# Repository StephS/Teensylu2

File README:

This board is a PROTOTYPE until the design is built and tested.

Version 0.9 is ready for production, earlier versions should not be used.

Please see Teensylu2_Pin_Map.htm for the correct pin mapping using the teensyduino library. Analog pins should use the analog pin reference.

The BOM is included. Please use parts of the same or higher ratings.

If you'd like to donate so I can buy the full version of Eagle, and make more cool stuff, please contact me through Google+

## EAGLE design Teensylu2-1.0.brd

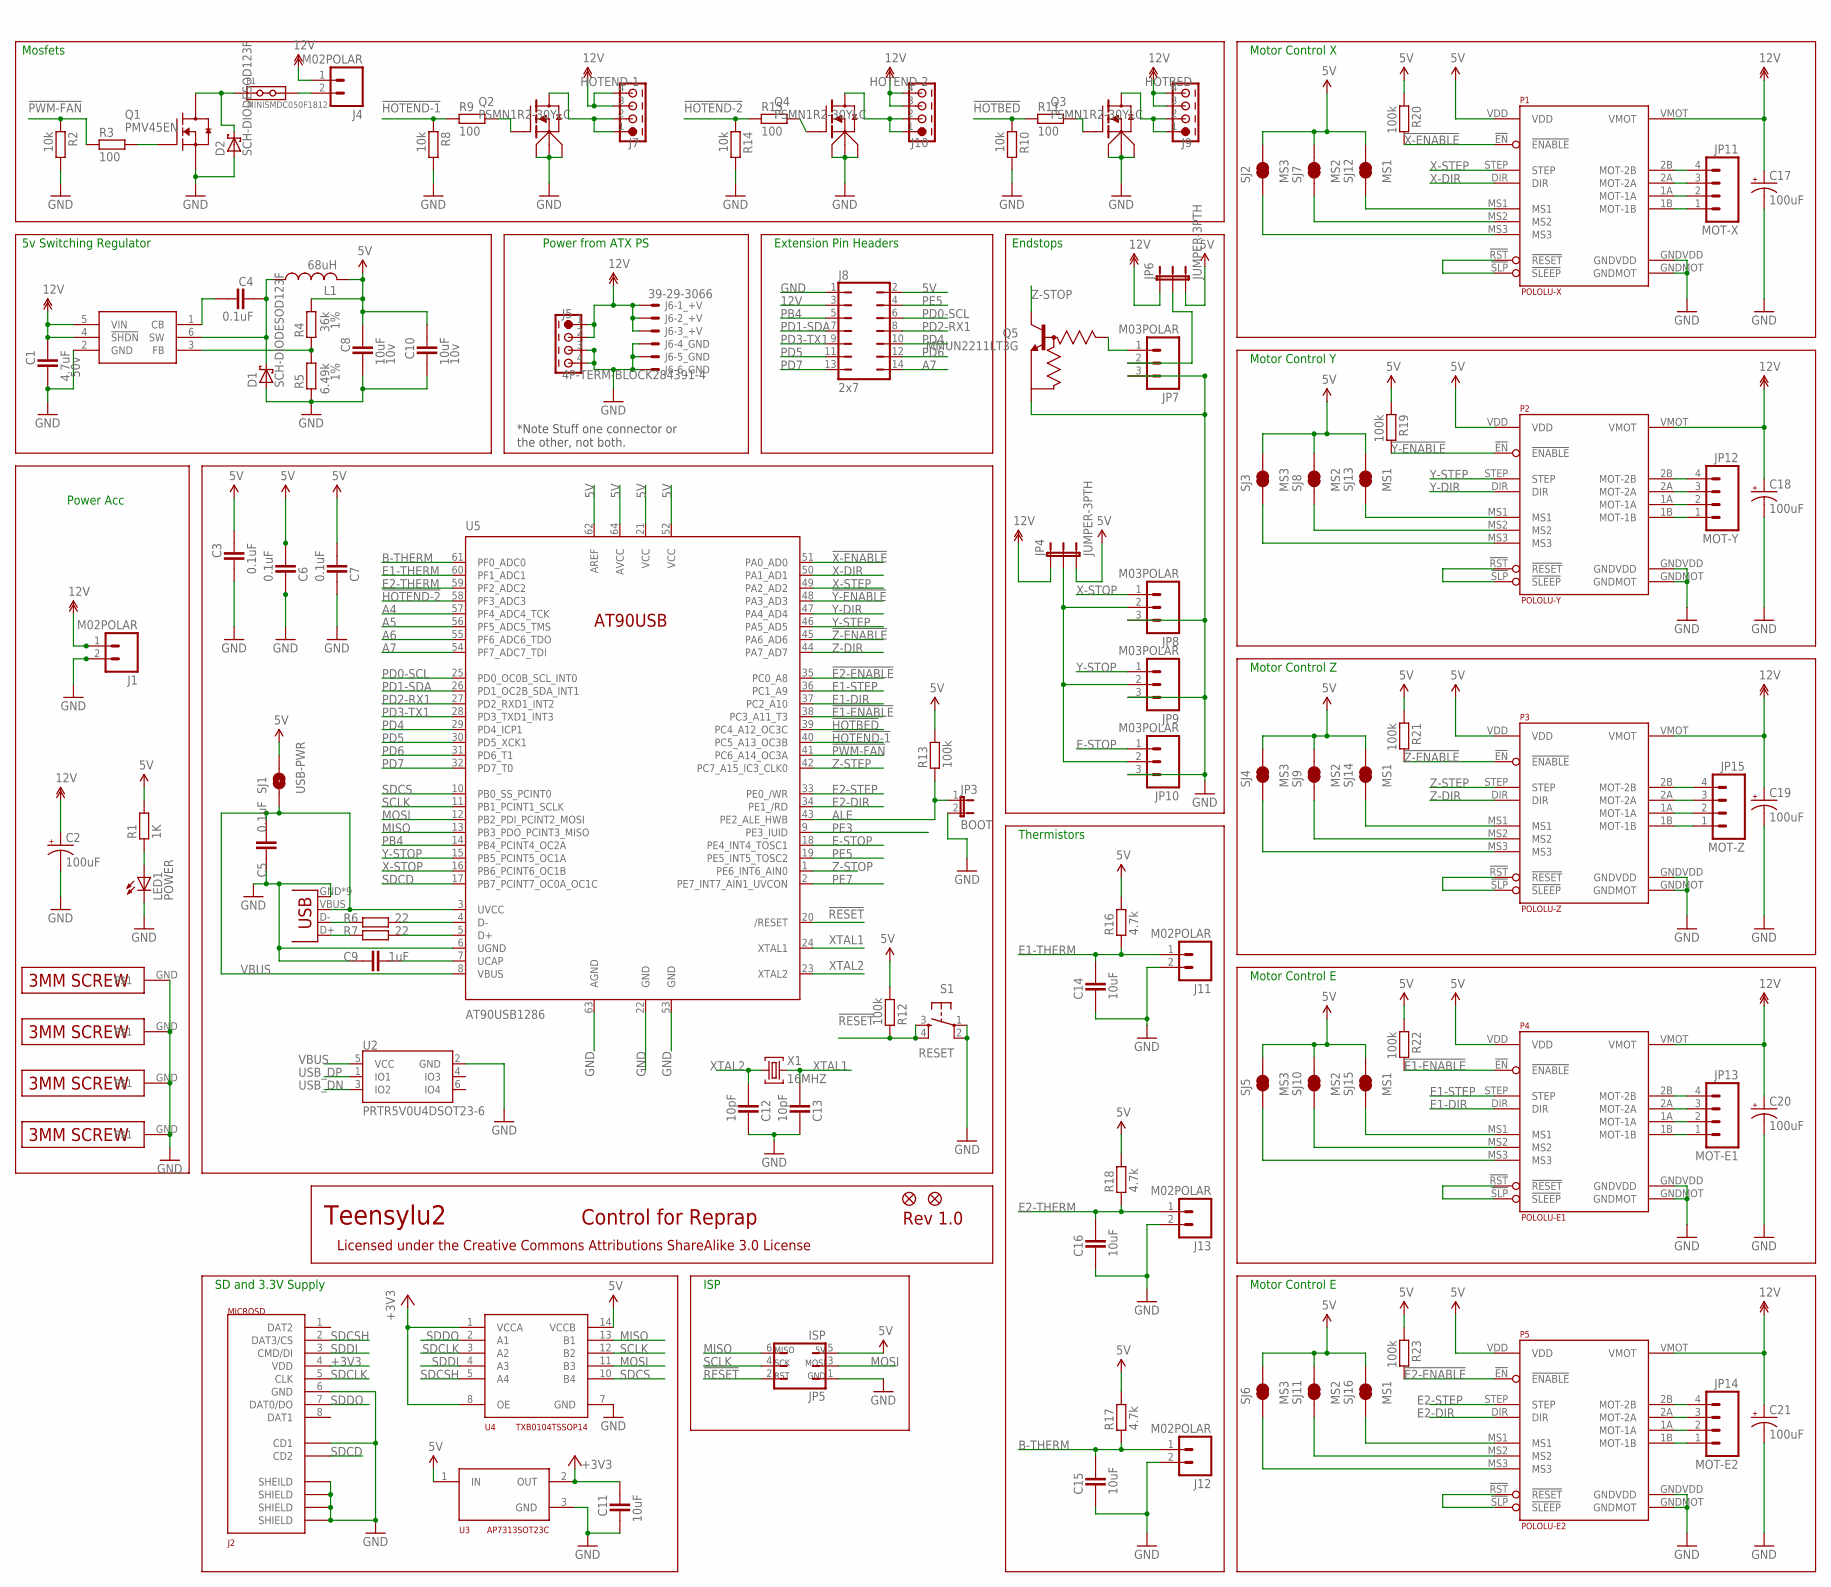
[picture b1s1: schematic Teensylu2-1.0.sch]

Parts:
C1: 4.7uF; CAPC3215X168N; TOLERANCE 10%; MANUFACTURER_PART_NUMBER UMK316AB7475KL-T
C2, C17, C18, C19, C20, C21: 100uF; PANASONIC_D; TOLERANCE 20%; MANUFACTURER_PART_NUMBER EEE-FTH101XAP
C3, C5, C6, C7: 0.1uF; CAPC1608X92N; TOLERANCE 10%; MANUFACTURER_PART_NUMBER GRM188R71C104KA01D
C4: 0.1uF; CAPC1608X92N; TOLERANCE 10%; MANUFACTURER_PART_NUMBER CL10B104KB8NNNC
C8, C10: 10uF; CAPC2012X145AN; TOLERANCE 10%; MANUFACTURER_PART_NUMBER GRM21BR71A106KE51L
C9: 1uF; CAPC1608X92N; TOLERANCE 20%; MANUFACTURER_PART_NUMBER CL10A105MO8NNNC
C11, C14, C15, C16: 10uF; CAPC1608X92N; TOLERANCE 20%; MANUFACTURER_PART_NUMBER GRM188R61C106MA73D
C12, C13: 10pF; CAPC1608X92N; TOLERANCE 5%; MANUFACTURER_PART_NUMBER CL10C100JB8NCNC
D1: SCH-DIODESOD123F; SOD123F; MANUFACTURER_PART_NUMBER PMEG4010CEH,115
D2: SCH-DIODESOD123F; SOD123F
F1: MINISMDC050F1812; MINISMDC
J1, J4, J11, J12, J13: M02POLAR; MOLEX-1X2; MANUFACTURER_PART_NUMBER 0022272021
J2: MICROSD; AMPHENOL-MICROSD
J3: USB-MICRO-PTH; USB-MICROB-PTH
J5: 4P-TERM-BLOCK284391-4; 284391-4
J6: 39-29-3066
J7: HOTEND-1; 282834-4
J8: 2x7; JP7Q; MANUFACTURER_PART_NUMBER M20-9980746
J9: HOTBED; 284391-4
J10: HOTEND-2; 282834-4
JP1, JP2: FIDUCIAL1X2.5; FIDUCIAL-1X2.5
JP3: BOOT; 1X02; MANUFACTURER_PART_NUMBER M20-9990246
JP4, JP6: JUMPER-3PTH; 1X03
JP5: ISP
JP7, JP8, JP9, JP10: M03POLAR; MOLEX-1X3; MANUFACTURER_PART_NUMBER 0022272031
JP11: MOT-X; MOLEX-1X4
JP12: MOT-Y; MOLEX-1X4
JP13: MOT-E1; MOLEX-1X4
JP14: MOT-E2; MOLEX-1X4
JP15: MOT-Z; MOLEX-1X4
L1: 68uH; SRN6045; MANUFACTURER_PART_NUMBER SRN6045-680M
LED1: POWER; CHIPLED_0805; MANUFACTURER_PART_NUMBER APT2012SGC
P1: POLOLU-X; POLOLU-STEPPER-PTH
P2: POLOLU-Y; POLOLU-STEPPER-PTH
P3: POLOLU-Z; POLOLU-STEPPER-PTH
P4: POLOLU-E1; POLOLU-STEPPER-PTH
P5: POLOLU-E2; POLOLU-STEPPER-PTH
Q1: PMV45EN; SOT23C; VOLTAGE 60V; MANUFACTURER_PART_NUMBER IRLML2060TRPBF
Q2, Q3, Q4: PSMN1R2-30YLC; LFPACK-POWERPAK-SO8
Q5: MMUN2211LT3G; SOT23C; MANUFACTURER_PART_NUMBER MMUN2211LT3G
R1: 1K; RESC1608X55N
R2, R8, R10, R14: 10k; RESC1608X55N
R3, R9, R11, R15: 100; RESC1608X55N
R4: 36k; RESC1608X55N; TOLERANCE 1%
R5: 6.49k; RESC1608X55N; TOLERANCE 1%
R6, R7: 22; RESC1608X55N
R12, R13, R19, R20, R21, R22, R23: 100k; RESC1608X55N
R16, R17, R18: 4.7k; RESC1608X55N
S1: RESET; TACTILE_SWITCH_SMD
SCREW1, SCREW2, SCREW3, SCREW4: 3MM-SCREW; PLATEDSCREW
SJ1: USB-PWR; SJ_2S-NO
SJ2, SJ3, SJ4, SJ5, SJ6: MS3; SJ_2S-TRACE
SJ7, SJ8, SJ9, SJ10, SJ11: MS2; SJ_2S-TRACE
SJ12, SJ13, SJ14, SJ15, SJ16: MS1; SJ_2S-TRACE
U1: LMR16006X; TSOT6
U2: PRTR5V0U4DSOT23-6; SOT23-6
U3: AP7313SOT23C; SOT23C
U4: TXB0104TSSOP14; TSSOP14
U5: AT90USB1286; TQFP64-2; MANUFACTURER_PART_NUMBER AT90USB1286
X1: 16MHZ; NDK-XTAL; MANUFACTURER_PART_NUMBER NX5032GA-16.000000MHZ-LN-CD-1

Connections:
5V: C3.1, C6.2, C7.2, C8.1, C10.1, J8.2, JP4.3, JP5.5, JP6.3, L1.2, P1.VDD, P2.VDD, P3.VDD, P4.VDD, P5.VDD, R1.2, R4.1, R12.2, R13.2, R16.2, R17.2, R18.2, R19.1, R20.1, R21.1, R22.1, R23.1, SJ1.2, SJ2.2, SJ3.2, SJ4.2, SJ5.2, SJ6.2, SJ7.2, SJ8.2, SJ9.2, SJ10.2, SJ11.2, SJ12.2, SJ13.2, SJ14.2, SJ15.2, SJ16.2, U3.1 (IN), U4.14 (VCCB), U5.21 (VCC), U5.52 (VCC), U5.62 (AREF), U5.64 (AVCC)
5VREG_CB: C4.2, U1.1 (CB)
5VREG_FB: R4.2, R5.1, U1.3 (FB)
5VREG_SW: C4.1, D1.C, L1.1, U1.6 (SW)
12V: C1.1, C2.+, C17.+, C18.+, C19.+, C20.+, C21.+, J1.1, J4.1, J5.1, J5.2, J6.1, J6.2, J6.3, J7.3, J7.4, J8.3, J9.3, J9.4, J10.3, J10.4, JP4.1, JP6.1, P1.VMOT, P2.VMOT, P3.VMOT, P4.VMOT, P5.VMOT, U1.4 (!SHDN), U1.5 (VIN)
!E1-ENABLE: P4.!EN (!ENABLE), R22.2, U5.38 (PC3_A11_T3)
!E2-ENABLE: P5.!EN (!ENABLE), R23.2, U5.35 (PC0_A8)
!HOTBED: R10.1, R11.1, U5.39 (PC4_A12_OC3C)
!HOTEND-1: R8.1, R9.1, U5.40 (PC5_A13_OC3B)
!HOTEND-2: R14.1, R15.1, U5.58 (PF3_ADC3)
!PWM-FAN: R2.1, R3.1, U5.41 (PC6_A14_OC3A)
!RESET: JP5.2, R12.1, S1.3, S1.4, U5.20 (/RESET)
!X-ENABLE: P1.!EN (!ENABLE), R20.2, U5.51 (PA0_AD0)
!Y-ENABLE: P2.!EN (!ENABLE), R19.2, U5.48 (PA3_AD3)
!Z-ENABLE: P3.!EN (!ENABLE), R21.2, U5.45 (PA6_AD6)
+3V3: C11.1, J2.4 (VDD), U3.2 (OUT), U4.1 (VCCA), U4.8 (OE)
A4: U5.57 (PF4_ADC4_TCK)
A5: U5.56 (PF5_ADC5_TMS)
A6: U5.55 (PF6_ADC6_TDO)
A7: J8.14, U5.54 (PF7_ADC7_TDI)
ALE: JP3.1, R13.1, U5.43 (PE2_ALE_HWB)
B-THERM: C15.2, J12.1, R17.1, U5.61 (PF0_ADC0)
E1-DIR: P4.DIR, U5.37 (PC2_A10)
E1-STEP: P4.STEP, U5.36 (PC1_A9)
E1-THERM: C14.2, J11.1, R16.1, U5.60 (PF1_ADC1)
E2-DIR: P5.DIR, U5.34 (PE1_/RD)
E2-MOT-1A: JP14.2, P5.1A (MOT-1A)
E2-MOT-1B: JP14.1, P5.1B (MOT-1B)
E2-MOT-2A: JP14.3, P5.2A (MOT-2A)
E2-MOT-2B: JP14.4, P5.2B (MOT-2B)
E2-STEP: P5.STEP, U5.33 (PE0_/WR)
E2-THERM: C16.2, J13.1, R18.1, U5.59 (PF2_ADC2)
E-MOT-1A: JP13.2, P4.1A (MOT-1A)
E-MOT-1B: JP13.1, P4.1B (MOT-1B)
E-MOT-2A: JP13.3, P4.2A (MOT-2A)
E-MOT-2B: JP13.4, P4.2B (MOT-2B)
E-MS1: P4.MS1, SJ15.1
E-MS2: P4.MS2, SJ10.1
E-MS3: P4.MS3, SJ5.1
E-MS4: P5.MS1, SJ16.1
E-MS5: P5.MS2, SJ11.1
E-MS6: P5.MS3, SJ6.1
E-RESETSLEEP: P4.!RST (!RESET), P4.!SLP (!SLEEP)
E-RESETSLEEP1: P5.!RST (!RESET), P5.!SLP (!SLEEP)
E-STOP: JP10.1, U5.18 (PE4_INT4_TOSC1)
ENDSTOP+V: JP4.2, JP8.2, JP9.2, JP10.2
GND: C1.2, C2.-, C3.2, C5.1, C6.1, C7.1, C8.2, C9.1, C10.2, C11.2, C12.1, C13.1, C14.1, C15.1, C16.1, C17.-, C18.-, C19.-, C20.-, C21.-, D1.A, D2.A, J1.2, J2.6 (GND), J2.C1 (SHEILD), J2.C2 (SHIELD), J2.C3 (SHIELD), J2.C4 (SHIELD), J2.CD1, J3.GND, J3.GND1 (GND), J3.GND2 (GND), J3.GND3 (GND), J3.GND4 (GND), J3.GND5 (GND), J3.GND6 (GND), J3.GND7 (GND), J3.GND8 (GND), J5.3, J5.4, J6.4, J6.5, J6.6, J8.1, J11.2, J12.2, J13.2, JP3.2, JP5.1, JP7.3, JP8.3, JP9.3, JP10.3, LED1.C, P1.GNDMOT, P1.GNDVDD, P2.GNDMOT, P2.GNDVDD, P3.GNDMOT, P3.GNDVDD, P4.GNDMOT, P4.GNDVDD, P5.GNDMOT, P5.GNDVDD, Q1.2 (S), Q2.1 (S1), Q2.2 (S2), Q2.3 (S3), Q3.1 (S1), Q3.2 (S2), Q3.3 (S3), Q4.1 (S1), Q4.2 (S2), Q4.3 (S3), Q5.2 (E), R2.2, R5.2, R8.2, R10.2, R14.2, S1.1, S1.2, SCREW1.GND, SCREW2.GND, SCREW3.GND, SCREW4.GND, U1.2 (GND), U2.2 (GND), U3.3 (GND), U4.7 (GND), U5.6 (UGND), U5.22 (GND), U5.53 (GND), U5.63 (AGND)
HOTBED-GND: J9.1, J9.2, Q3.5-8 (D)
HOTEND-GND: J7.1, J7.2, Q2.5-8 (D)
HOTEND-GND1: J10.1, J10.2, Q4.5-8 (D)
MISO: JP5.6, U4.13 (B1), U5.13 (PB3_PDO_PCINT3_MISO)
MOSI: JP5.3, U4.11 (B3), U5.12 (PB2_PDI_PCINT2_MOSI)
unnamed: LED1.A, R1.1
unnamed: Q3.4 (G), R11.2
unnamed: R6.2, U5.4 (D-)
unnamed: R7.2, U5.5 (D+)
unnamed: F1.P$2, J4.2
unnamed: D2.C, F1.P$1, Q1.3 (D)
unnamed: Q1.1 (G), R3.2
unnamed: Q2.4 (G), R9.2
unnamed: Q4.4 (G), R15.2
PB4: J8.5, U5.14 (PB4_PCINT4_OC2A)
PD0-SCL: J8.6, U5.25 (PD0_OC0B_SCL_INT0)
PD1-SDA: J8.7, U5.26 (PD1_OC2B_SDA_INT1)
PD2-RX1: J8.8, U5.27 (PD2_RXD1_INT2)
PD3-TX1: J8.9, U5.28 (PD3_TXD1_INT3)
PD4: J8.10, U5.29 (PD4_ICP1)
PD5: J8.11, U5.30 (PD5_XCK1)
PD6: J8.12, U5.31 (PD6_T1)
PD7: J8.13, U5.32 (PD7_T0)
PE3: U5.9 (PE3_IUID)
PE5: J8.4, U5.19 (PE5_INT5_TOSC2)
PE7: U5.2 (PE7_INT7_AIN1_UVCON)
SCLK: JP5.4, U4.12 (B2), U5.11 (PB1_PCINT1_SCLK)
SDCD: J2.CD2, U5.17 (PB7_PCINT7_OC0A_OC1C)
SDCLK: J2.5 (CLK), U4.3 (A2)
SDCS: U4.10 (B4), U5.10 (PB0_SS_PCINT0)
SDCSH: J2.2 (DAT3/CS), U4.5 (A4)
SDDI: J2.3 (CMD/DI), U4.4 (A3)
SDDO: J2.7 (DAT0/DO), U4.2 (A1)
UCAP: C9.2, U5.7 (UCAP)
USB_DN: J3.D-, R6.1, U2.3 (IO2)
USB_DP: J3.D+, R7.1, U2.1 (IO1)
VBUS: C5.2, J3.VBUS, SJ1.1, U2.5 (VCC), U5.3 (UVCC), U5.8 (VBUS)
X-DIR: P1.DIR, U5.50 (PA1_AD1)
X-MOT-1A: JP11.2, P1.1A (MOT-1A)
X-MOT-1B: JP11.1, P1.1B (MOT-1B)
X-MOT-2A: JP11.3, P1.2A (MOT-2A)
X-MOT-2B: JP11.4, P1.2B (MOT-2B)
X-MS1: P1.MS1, SJ12.1
X-MS2: P1.MS2, SJ7.1
X-MS3: P1.MS3, SJ2.1
X-RESETSLEEP: P1.!RST (!RESET), P1.!SLP (!SLEEP)
X-STEP: P1.STEP, U5.49 (PA2_AD2)
X-STOP: JP8.1, U5.16 (PB6_PCINT6_OC1B)
XTAL1: C13.2, U5.24 (XTAL1), X1.P$2 (2)
XTAL2: C12.2, U5.23 (XTAL2), X1.P$1 (1)
Y-DIR: P2.DIR, U5.47 (PA4_AD4)
Y-MOT-1A: JP12.2, P2.1A (MOT-1A)
Y-MOT-1B: JP12.1, P2.1B (MOT-1B)
Y-MOT-2A: JP12.3, P2.2A (MOT-2A)
Y-MOT-2B: JP12.4, P2.2B (MOT-2B)
Y-MS1: P2.MS1, SJ13.1
Y-MS2: P2.MS2, SJ8.1
Y-MS3: P2.MS3, SJ3.1
Y-RESETSLEEP: P2.!RST (!RESET), P2.!SLP (!SLEEP)
Y-STEP: P2.STEP, U5.46 (PA5_AD5)
Y-STOP: JP9.1, U5.15 (PB5_PCINT5_OC1A)
Z-DIR: P3.DIR, U5.44 (PA7_AD7)
Z-MOT-1A: JP15.2, P3.1A (MOT-1A)
Z-MOT-1B: JP15.1, P3.1B (MOT-1B)
Z-MOT-2A: JP15.3, P3.2A (MOT-2A)
Z-MOT-2B: JP15.4, P3.2B (MOT-2B)
Z-MS1: P3.MS1, SJ14.1
Z-MS2: P3.MS2, SJ9.1
Z-MS3: P3.MS3, SJ4.1
Z-RESETSLEEP: P3.!RST (!RESET), P3.!SLP (!SLEEP)
Z-STEP: P3.STEP, U5.42 (PC7_A15_IC3_CLK0)
Z-STOP: Q5.3 (C), U5.1 (PE6_INT6_AIN0)
Z-STOP-BIAS: JP7.1, Q5.1 (B)
Z-STOP-SUPPLY: JP6.2, JP7.2

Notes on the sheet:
Motor Control X
Motor Control Y
Motor Control Z
Motor Control E
ISP
Thermistors
Endstops
Mosfets
Power Acc
Teensylu2
Rev 1.0
Control for Reprap
Licensed under the Creative Commons Attributions ShareAlike 3.0 License
Extension Pin Headers
Power from ATX PS
5v Switching Regulator
SD and 3.3V Supply
*Note Stuff one connector or the other, not both.

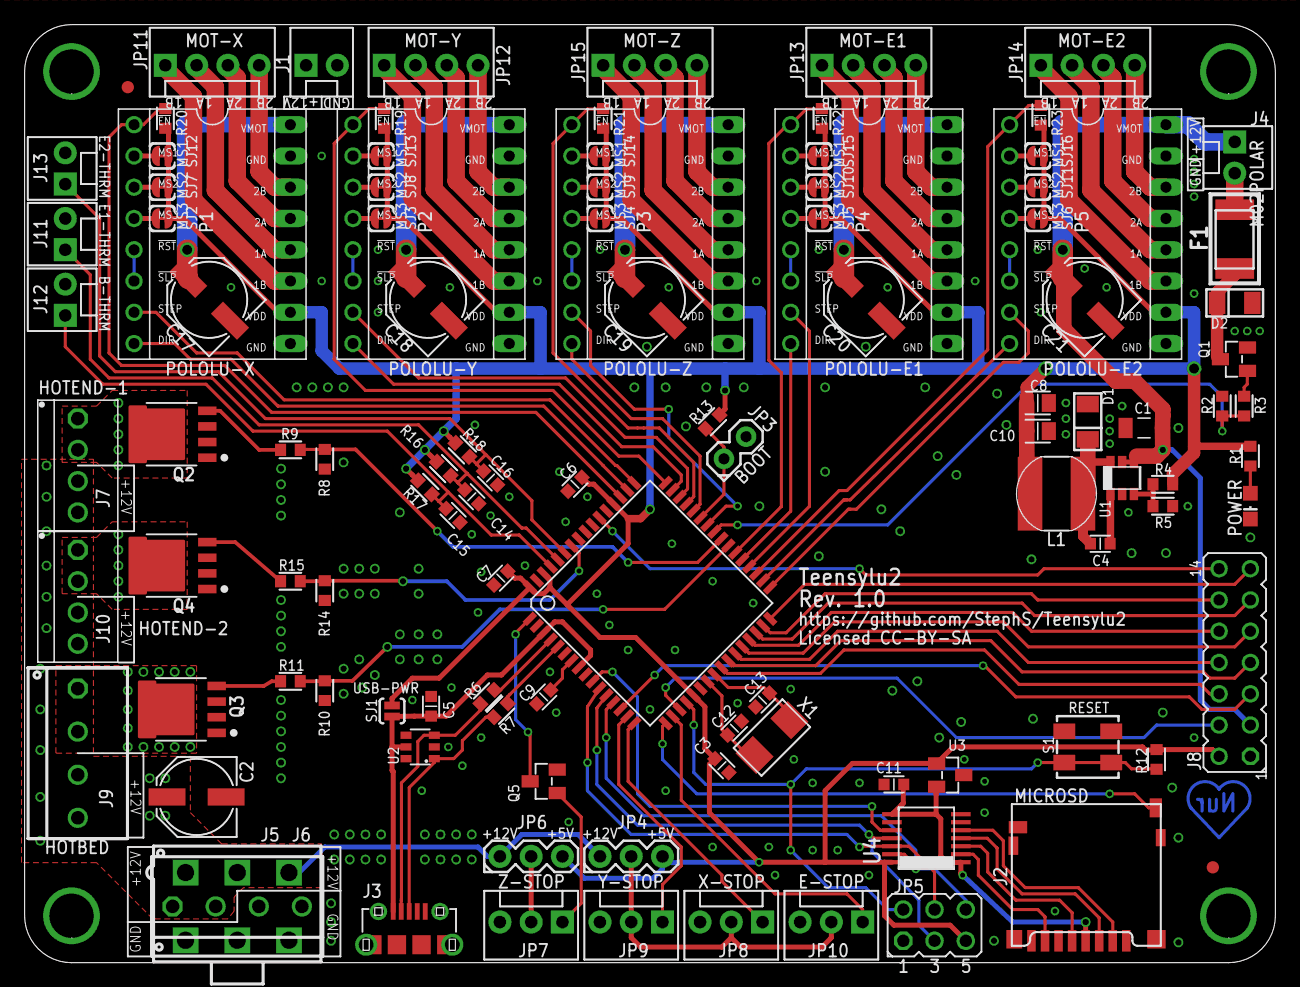
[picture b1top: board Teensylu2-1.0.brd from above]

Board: 2 copper layers, 101.6 x 76.2 mm, 114 parts (0 on the bottom side), 116 nets.

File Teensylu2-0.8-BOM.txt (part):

Partlist exported from C:/Users/stshalt/Documents/Teensylu2/Teensylu2-0.8.sch at 4/24/2015 5:08:34 PM

Part   Value                 Device                     Package             Description                                  CURRENT DCR   ESR    INDUCTANCE IRMS MANUFACTURER            MANUFACTURER_PART_NUMBER      RDS_ON   REVERSE_VOLTAGE TOLERANCE VDC VGS   VOLTAGE VOLTAGE_OUTPUT
C1     4.7uF                 CAPACITOR_1206             CAPC3215X168N                                                                                         Yaiyo Yuden             UMK316AB7475KL-T                                                 50v                             
C2     100uF                 CPOL-USD                   PANASONIC_D         POLARIZED CAPACITOR, American symbol                                              Panasonic               EEE-FTH101XAP                                          20%       50v                             
C3     0.1uF                 CAPACITOR_0603             CAPC1608X92N                                                                                          Murata                  GRM188R71C104KA01D                                     10%       16v                             
C4     0.1uF                 CAPACITOR_0603             CAPC1608X92N                                                                                          Samsung                 CL10B104KB8NNNC                                        10%       50V                             
C5     0.1uf                 CAPACITOR_0603             CAPC1608X92N                                                                                                                                                                                                                   
C6     0.1uF                 CAPACITOR_0603             CAPC1608X92N                                                                                          Murata                  GRM188R71C104KA01D                                     10%       16V                             
C7     0.1uF                 CAPACITOR_0603             CAPC1608X92N                                                                                          Murata                  GRM188R71C104KA01D                                     10%       16v                             
C8     10uF                  CAPACITOR_0805             CAPC2012X145AN                                                                 0.0030                 Murata                  GRM21BR71A106KE51L                                     10%       10v                             
C9     1uf                   CAPACITOR_0603             CAPC1608X92N                                                                                          Samsung                 CL10A105MO8NNNC                                        20%                 16                    
C10    10uF                  CAPACITOR_0805             CAPC2012X145AN                                                                 0.0030                 Murata                  GRM21BR71A106KE51L                                     10%       10v                             
C11    10uF                  CAPACITOR_0603             CAPC1608X92N                                                                                          Murata                  GRM188R61C106MA73D                                     20%                 16V                   
C12    10pF                  CAPACITOR_0603             CAPC1608X92N                                                                                          Samsung                 CL10C100JB8NCNC                                        5%                  50V                   
C13    10pF                  CAPACITOR_0603             CAPC1608X92N                                                                                          Samsung                 CL10C100JB8NCNC                                        5%                  50V                   
C14    10uF                  CAPACITOR_0603             CAPC1608X92N                                                                                          Murata                  GRM188R61C106MA73D                                     20%                 16V                   
C15    10uF                  CAPACITOR_0603             CAPC1608X92N                                                                                          Murata                  GRM188R61C106MA73D                                     20%                 16V                   
C16    10uF                  CAPACITOR_0603             CAPC1608X92N                                                                                          Murata                  GRM188R61C106MA73D                                     20%                 16V                   
C17    100uF                 CPOL-USD                   PANASONIC_D         POLARIZED CAPACITOR, American symbol                                              Panasonic               EEE-FTH101XAP                                          20%       50v                             
C18    100uF                 CPOL-USD                   PANASONIC_D         POLARIZED CAPACITOR, American symbol                                              Panasonic               EEE-FTH101XAP                                          20%       50v                             
C19    100uF                 CPOL-USD                   PANASONIC_D         POLARIZED CAPACITOR, American symbol                                              Panasonic               EEE-FTH101XAP                                          20%       50v                             
C20    100uF                 CPOL-USD                   PANASONIC_D         POLARIZED CAPACITOR, American symbol                                              Panasonic               EEE-FTH101XAP                                          20%       50v                             
C21    100uF                 CPOL-USD                   PANASONIC_D         POLARIZED CAPACITOR, American symbol                                              Panasonic               EEE-FTH101XAP                                          20%       50v                             
D1     SCH-DIODESOD123F      SCH-DIODESOD123F           SOD123F             Schottky Diodes                              1A                                   NXP Semiconductors      PMEG4010CEH,115                        40V                                                       
D2     SCH-DIODESOD123F      SCH-DIODESOD123F           SOD123F             Schottky Diodes                              1A                                   NXP Semiconductors      PMEG4010CEH,115                        40V                                                       
F1     MINISMDC050F1812      MINISMDC050F1812           MINISMDC                                                         0.5A                                 TE Connectivity         MINISMDC050F-2                                                                                   
J1     12VPWR                M02POLAR                   MOLEX-1X2           Header 2                                                                                                                                                                                                   
J2     MICROSD               MICROSD                    AMPHENOL-MICROSD                                                                                      Amphenol                114-00841-68                                                                                     
J3     USB-MICRO-PTH         USB-MICRO-PTH              USB-MICROB-PTH      USB Connectors                                                                    FCI                     10118194-0001LF                                                                                  
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
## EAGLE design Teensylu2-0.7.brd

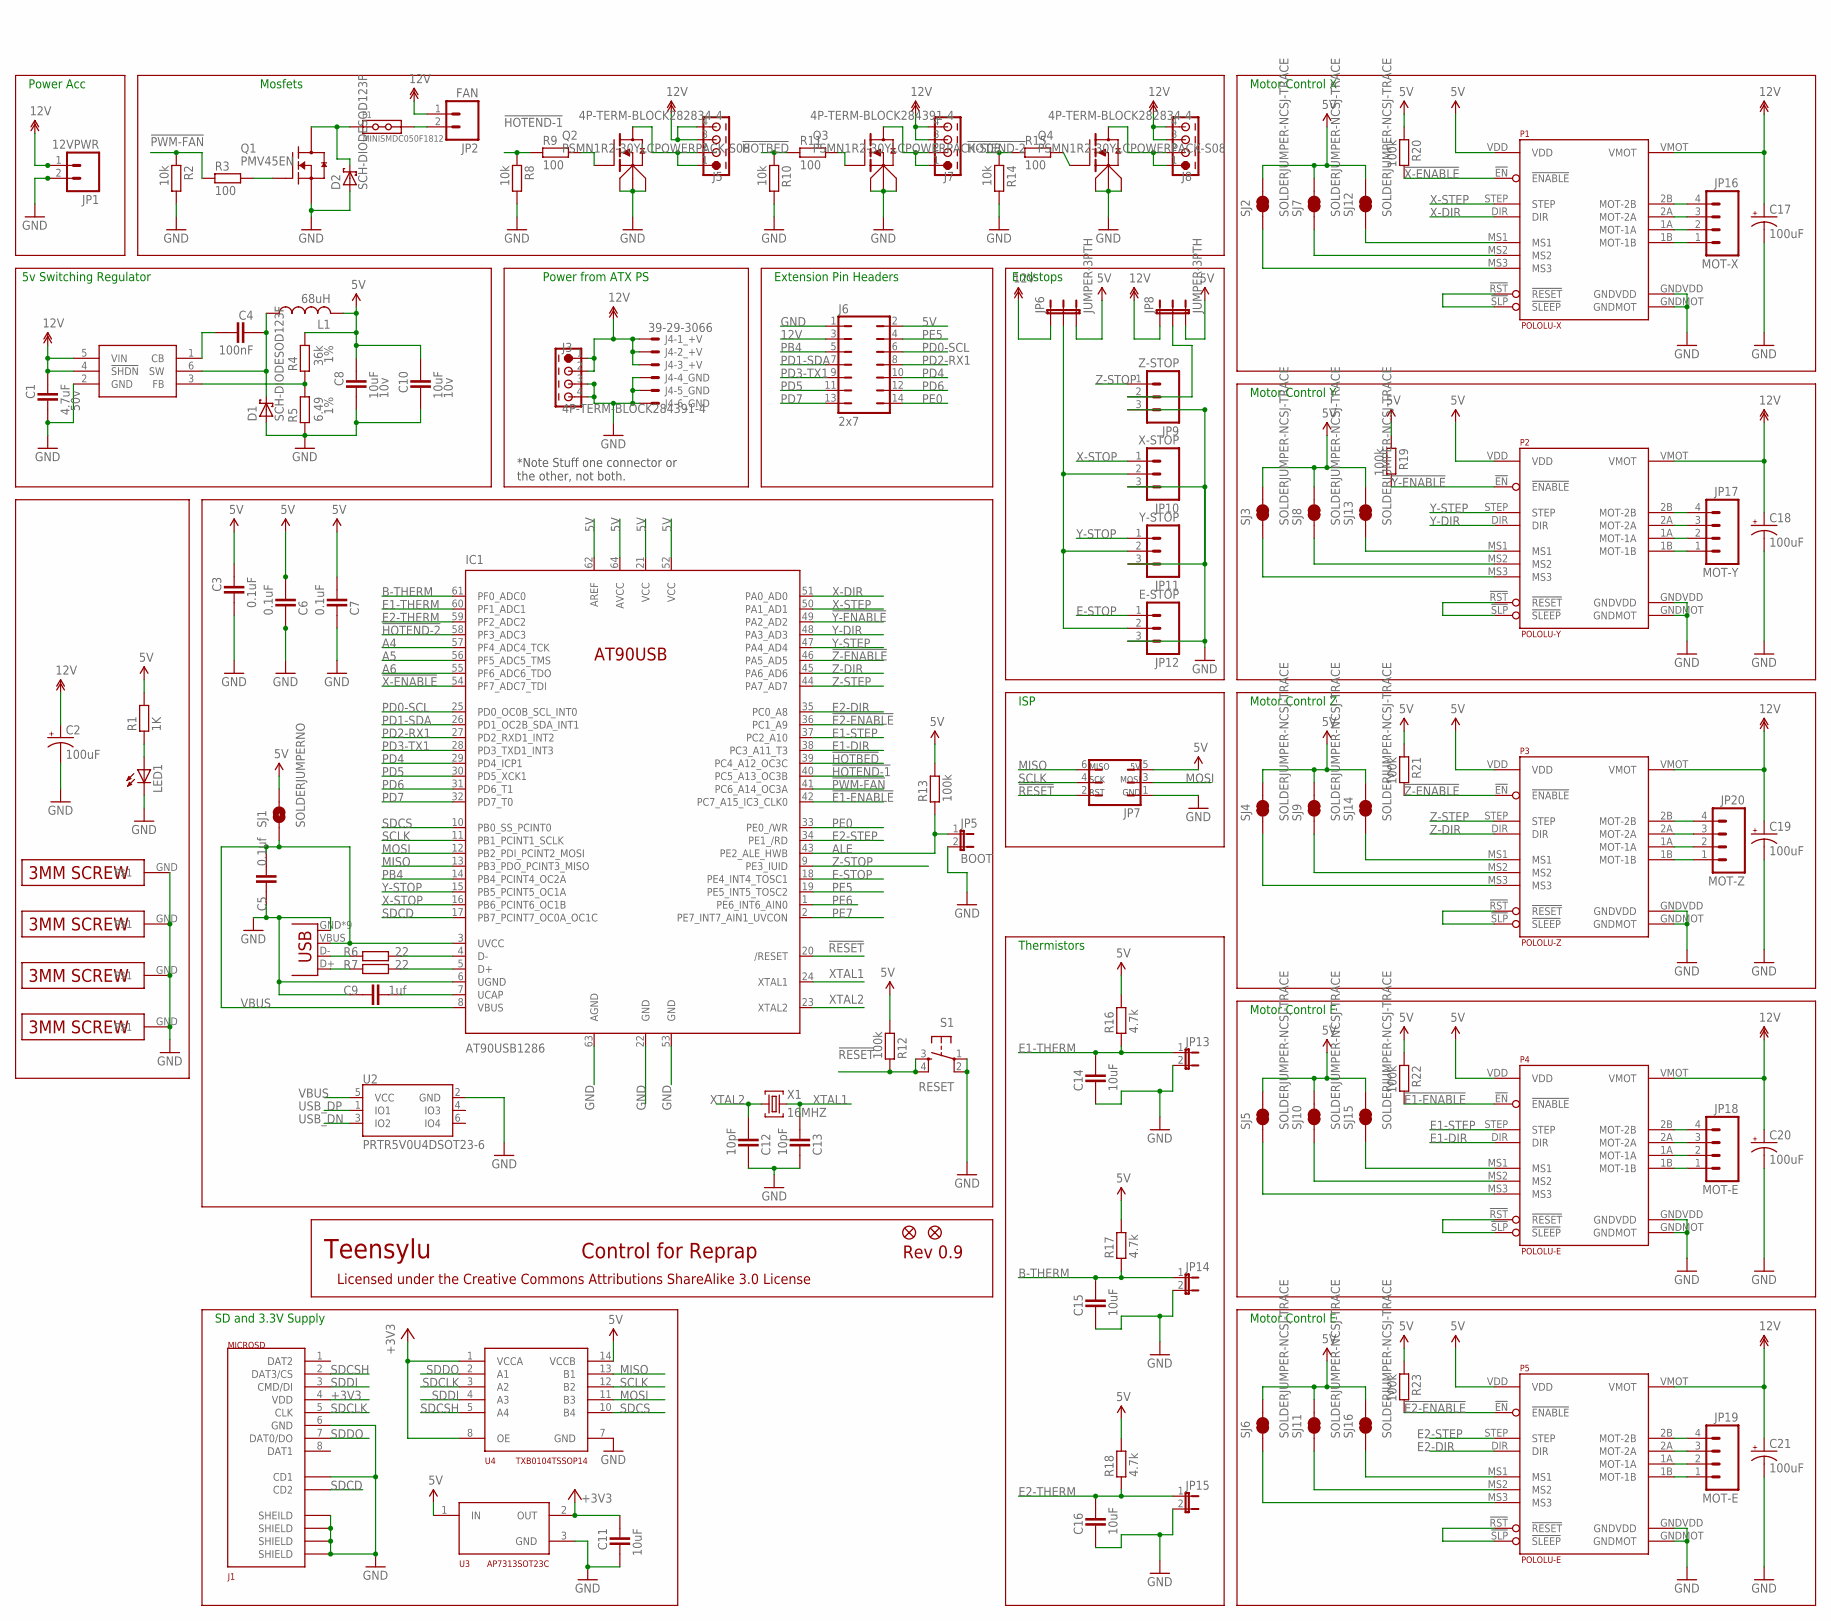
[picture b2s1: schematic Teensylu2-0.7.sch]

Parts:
C1: 4.7uF; CAPC2012X145AN
C2, C17, C18, C19, C20, C21: 100uF; PANASONIC_D; TOLERANCE 20%; MANUFACTURER_PART_NUMBER EEE-FTH101XAP
C3, C6, C7: 0.1uF; CAPC1608X92N
C4: 100nF; CAPC1608X92N
C5: 0.1uf; CAPC1608X92N
C8, C10: 10uF; CAPC2012X145AN
C9: 1uf; CAPC1608X92N
C11, C14, C15, C16: 10uF; CAPC1608X92N
C12, C13: 10pF; CAPC1608X92N
D1: SCH-DIODESOD123F; SOD123F; MANUFACTURER_PART_NUMBER PMEG4010CEH,115
D2: SCH-DIODESOD123F; SOD123F
F1: MINISMDC050F1812; MINISMDC
IC1: AT90USB1286; TQFP64-2
J1: MICROSD; AMPHENOL-MICROSD
J2: USB-MICRO-PTH; USB-MICROB-PTH
J3, J7: 4P-TERM-BLOCK284391-4; 284391-4
J4: 39-29-3066
J5, J8: 4P-TERM-BLOCK282834-4; 282834-4
J6: 2x7; JP7Q
JP1: 12VPWR; MOLEX-1X2
JP2: FAN; MOLEX-1X2
JP3, JP4: FIDUCIAL1X2.5; FIDUCIAL-1X2.5
JP5: BOOT; 1X02
JP6, JP8: JUMPER-3PTH; 1X03
JP7: PROGHEADER; ISP
JP9: Z-STOP; MOLEX-1X3
JP10: X-STOP; MOLEX-1X3
JP11: Y-STOP; MOLEX-1X3
JP12: E-STOP; MOLEX-1X3
JP13, JP14, JP15: JUMPER-2PTH; 1X02
JP16: MOT-X; MOLEX-1X4
JP17: MOT-Y; MOLEX-1X4
JP18, JP19: MOT-E; MOLEX-1X4
JP20: MOT-Z; MOLEX-1X4
L1: 68uH; SRN6045; MANUFACTURER_PART_NUMBER SRN6045-680M
LED1: LEDCHIPLED_0805; CHIPLED_0805
P1: POLOLU-X; POLOLU-STEPPER-PTH
P2: POLOLU-Y; POLOLU-STEPPER-PTH
P3: POLOLU-Z; POLOLU-STEPPER-PTH
P4, P5: POLOLU-E; POLOLU-STEPPER-PTH
Q1: PMV45EN; SOT23C; VOLTAGE 60V; MANUFACTURER_PART_NUMBER IRLML2060TRPBF
Q2, Q3, Q4: PSMN1R2-30YLCPOWERPACK-S08; LFPACK-POWERPAK-SO8
R1: 1K; RESC1608X55N
R2, R8, R10, R14: 10k; RESC1608X55N
R3, R9, R11, R15: 100; RESC1608X55N
R4: 36k; RESC1608X55N; TOLERANCE 1%
R5: 6.49; RESC1608X55N; TOLERANCE 1%
R6, R7: 22; RESC1608X55N
R12, R13, R19, R20, R21, R22, R23: 100k; RESC1608X55N
R16, R17, R18: 4.7k; RESC1608X55N
S1: RESET; TACTILE-PTH
SCREW1, SCREW2, SCREW3, SCREW4: 3MM-SCREW; PLATEDSCREW
SJ1: SOLDERJUMPERNO; SJ_2S-NO
SJ2, SJ3, SJ4, SJ5, SJ6, SJ7, SJ8, SJ9, SJ10, SJ11, SJ12, SJ13, SJ14, SJ15, SJ16: SOLDERJUMPER-NCSJ-TRACE; SJ_2S-TRACE
U1: LMR16006X; TSOT6
U2: PRTR5V0U4DSOT23-6; SOT23-6
U3: AP7313SOT23C; SOT23C
U4: TXB0104TSSOP14; TSSOP14
X1: 16MHZ; NDK-XTAL

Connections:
5V: C3.1, C6.2, C7.2, C8.1, C10.1, IC1.21 (VCC), IC1.52 (VCC), IC1.62 (AREF), IC1.64 (AVCC), J6.2, JP6.3, JP7.5, JP8.3, L1.2, P1.VDD, P2.VDD, P3.VDD, P4.VDD, P5.VDD, R1.2, R4.1, R12.2, R13.2, R16.2, R17.2, R18.2, R19.1, R20.1, R21.1, R22.1, R23.1, SJ1.2, SJ2.2, SJ3.2, SJ4.2, SJ5.2, SJ6.2, SJ7.2, SJ8.2, SJ9.2, SJ10.2, SJ11.2, SJ12.2, SJ13.2, SJ14.2, SJ15.2, SJ16.2, U3.1 (IN), U4.14 (VCCB)
5VREG_CB: C4.2, U1.1 (CB)
5VREG_FB: R4.2, R5.1, U1.3 (FB)
5VREG_SW: C4.1, D1.C, L1.1, U1.6 (SW)
12V: C1.1, C2.+, C17.+, C18.+, C19.+, C20.+, C21.+, J3.1, J3.2, J4.1, J4.2, J4.3, J5.3, J5.4, J6.3, J7.3, J7.4, J8.3, J8.4, JP1.1, JP2.1, JP6.1, JP8.1, P1.VMOT, P2.VMOT, P3.VMOT, P4.VMOT, P5.VMOT, U1.4 (!SHDN), U1.5 (VIN)
!E1-ENABLE: IC1.42 (PC7_A15_IC3_CLK0), P4.!EN (!ENABLE), R22.2
!E2-ENABLE: IC1.36 (PC1_A9), P5.!EN (!ENABLE), R23.2
!HOTBED: IC1.39 (PC4_A12_OC3C), R10.1, R11.1
!HOTEND-1: IC1.40 (PC5_A13_OC3B), R8.1, R9.1
!HOTEND-2: IC1.58 (PF3_ADC3), R14.1, R15.1
!PWM-FAN: IC1.41 (PC6_A14_OC3A), R2.1, R3.1
!RESET: IC1.20 (/RESET), JP7.2, R12.1, S1.3, S1.4
!X-ENABLE: IC1.54 (PF7_ADC7_TDI), P1.!EN (!ENABLE), R20.2
!Y-ENABLE: IC1.49 (PA2_AD2), P2.!EN (!ENABLE), R19.2
!Z-ENABLE: IC1.46 (PA5_AD5), P3.!EN (!ENABLE), R21.2
+3V3: C11.1, J1.4 (VDD), U3.2 (OUT), U4.1 (VCCA), U4.8 (OE)
A4: IC1.57 (PF4_ADC4_TCK)
A5: IC1.56 (PF5_ADC5_TMS)
A6: IC1.55 (PF6_ADC6_TDO)
ALE: IC1.43 (PE2_ALE_HWB), JP5.1, R13.1
B-THERM: C15.2, IC1.61 (PF0_ADC0), JP14.1, R17.1
E1-DIR: IC1.38 (PC3_A11_T3), P4.DIR
E1-STEP: IC1.37 (PC2_A10), P4.STEP
E1-THERM: C14.2, IC1.60 (PF1_ADC1), JP13.1, R16.1
E2-DIR: IC1.35 (PC0_A8), P5.DIR
E2-STEP: IC1.34 (PE1_/RD), P5.STEP
E2-THERM: C16.2, IC1.59 (PF2_ADC2), JP15.1, R18.1
E-MOT-1A: JP18.2, P4.1A (MOT-1A)
E-MOT-1A1: JP19.2, P5.1A (MOT-1A)
E-MOT-1B: JP18.1, P4.1B (MOT-1B)
E-MOT-1B1: JP19.1, P5.1B (MOT-1B)
E-MOT-2A: JP18.3, P4.2A (MOT-2A)
E-MOT-2A1: JP19.3, P5.2A (MOT-2A)
E-MOT-2B: JP18.4, P4.2B (MOT-2B)
E-MOT-2B1: JP19.4, P5.2B (MOT-2B)
E-MS1: P4.MS1, SJ15.1
E-MS2: P4.MS2, SJ10.1
E-MS3: P4.MS3, SJ5.1
E-MS4: P5.MS1, SJ16.1
E-MS5: P5.MS2, SJ11.1
E-MS6: P5.MS3, SJ6.1
E-RESETSLEEP: P4.!RST (!RESET), P4.!SLP (!SLEEP)
E-RESETSLEEP1: P5.!RST (!RESET), P5.!SLP (!SLEEP)
E-STOP: IC1.18 (PE4_INT4_TOSC1), JP12.1
ENDSTOP+V: JP6.2, JP10.2, JP11.2, JP12.2
GND: C1.2, C2.-, C3.2, C5.1, C6.1, C7.1, C8.2, C9.1, C10.2, C11.2, C12.1, C13.1, C14.1, C15.1, C16.1, C17.-, C18.-, C19.-, C20.-, C21.-, D1.A, D2.A, IC1.6 (UGND), IC1.22 (GND), IC1.53 (GND), IC1.63 (AGND), J1.6 (GND), J1.C1 (SHEILD), J1.C2 (SHIELD), J1.C3 (SHIELD), J1.C4 (SHIELD), J1.CD1, J2.GND, J2.GND1 (GND), J2.GND2 (GND), J2.GND3 (GND), J2.GND4 (GND), J2.GND5 (GND), J2.GND6 (GND), J2.GND7 (GND), J2.GND8 (GND), J3.3, J3.4, J4.4, J4.5, J4.6, J6.1, JP1.2, JP5.2, JP7.1, JP9.3, JP10.3, JP11.3, JP12.3, JP13.2, JP14.2, JP15.2, LED1.C, P1.GNDMOT, P1.GNDVDD, P2.GNDMOT, P2.GNDVDD, P3.GNDMOT, P3.GNDVDD, P4.GNDMOT, P4.GNDVDD, P5.GNDMOT, P5.GNDVDD, Q1.2 (S), Q2.1 (S1), Q2.2 (S2), Q2.3 (S3), Q3.1 (S1), Q3.2 (S2), Q3.3 (S3), Q4.1 (S1), Q4.2 (S2), Q4.3 (S3), R2.2, R5.2, R8.2, R10.2, R14.2, S1.1, S1.2, SCREW1.GND, SCREW2.GND, SCREW3.GND, SCREW4.GND, U1.2 (GND), U2.2 (GND), U3.3 (GND), U4.7 (GND)
HOTBED-GND: J7.1, J7.2, Q3.5-8 (D)
HOTEND-GND: J5.1, J5.2, Q2.5-8 (D)
HOTEND-GND1: J8.1, J8.2, Q4.5-8 (D)
MISO: IC1.13 (PB3_PDO_PCINT3_MISO), JP7.6, U4.13 (B1)
MOSI: IC1.12 (PB2_PDI_PCINT2_MOSI), JP7.3, U4.11 (B3)
unnamed: LED1.A, R1.1
unnamed: Q3.4 (G), R11.2
unnamed: IC1.4 (D-), R6.2
unnamed: IC1.5 (D+), R7.2
unnamed: F1.P$2, JP2.2
unnamed: D2.C, F1.P$1, Q1.3 (D)
unnamed: Q1.1 (G), R3.2
unnamed: Q2.4 (G), R9.2
unnamed: Q4.4 (G), R15.2
PB4: IC1.14 (PB4_PCINT4_OC2A), J6.5
PD0-SCL: IC1.25 (PD0_OC0B_SCL_INT0), J6.6
PD1-SDA: IC1.26 (PD1_OC2B_SDA_INT1), J6.7
PD2-RX1: IC1.27 (PD2_RXD1_INT2), J6.8
PD3-TX1: IC1.28 (PD3_TXD1_INT3), J6.9
PD4: IC1.29 (PD4_ICP1), J6.10
PD5: IC1.30 (PD5_XCK1), J6.11
PD6: IC1.31 (PD6_T1), J6.12
PD7: IC1.32 (PD7_T0), J6.13
PE0: IC1.33 (PE0_/WR), J6.14
PE5: IC1.19 (PE5_INT5_TOSC2), J6.4
PE6: IC1.1 (PE6_INT6_AIN0)
PE7: IC1.2 (PE7_INT7_AIN1_UVCON)
SCLK: IC1.11 (PB1_PCINT1_SCLK), JP7.4, U4.12 (B2)
SDCD: IC1.17 (PB7_PCINT7_OC0A_OC1C), J1.CD2
SDCLK: J1.5 (CLK), U4.3 (A2)
SDCS: IC1.10 (PB0_SS_PCINT0), U4.10 (B4)
SDCSH: J1.2 (DAT3/CS), U4.5 (A4)
SDDI: J1.3 (CMD/DI), U4.4 (A3)
SDDO: J1.7 (DAT0/DO), U4.2 (A1)
UCAP: C9.2, IC1.7 (UCAP)
USB_DN: J2.D-, R6.1, U2.3 (IO2)
USB_DP: J2.D+, R7.1, U2.1 (IO1)
VBUS: C5.2, IC1.3 (UVCC), IC1.8 (VBUS), J2.VBUS, SJ1.1, U2.5 (VCC)
X-DIR: IC1.51 (PA0_AD0), P1.DIR
X-MOT-1A: JP16.2, P1.1A (MOT-1A)
X-MOT-1B: JP16.1, P1.1B (MOT-1B)
X-MOT-2A: JP16.3, P1.2A (MOT-2A)
X-MOT-2B: JP16.4, P1.2B (MOT-2B)
X-MS1: P1.MS1, SJ12.1
X-MS2: P1.MS2, SJ7.1
X-MS3: P1.MS3, SJ2.1
X-RESETSLEEP: P1.!RST (!RESET), P1.!SLP (!SLEEP)
X-STEP: IC1.50 (PA1_AD1), P1.STEP
X-STOP: IC1.16 (PB6_PCINT6_OC1B), JP10.1
XTAL1: C13.2, IC1.24 (XTAL1), X1.P$2 (2)
XTAL2: C12.2, IC1.23 (XTAL2), X1.P$1 (1)
Y-DIR: IC1.48 (PA3_AD3), P2.DIR
Y-MOT-1A: JP17.2, P2.1A (MOT-1A)
Y-MOT-1B: JP17.1, P2.1B (MOT-1B)
Y-MOT-2A: JP17.3, P2.2A (MOT-2A)
Y-MOT-2B: JP17.4, P2.2B (MOT-2B)
Y-MS1: P2.MS1, SJ13.1
Y-MS2: P2.MS2, SJ8.1
Y-MS3: P2.MS3, SJ3.1
Y-RESETSLEEP: P2.!RST (!RESET), P2.!SLP (!SLEEP)
Y-STEP: IC1.47 (PA4_AD4), P2.STEP
Y-STOP: IC1.15 (PB5_PCINT5_OC1A), JP11.1
Z-DIR: IC1.45 (PA6_AD6), P3.DIR
Z-MOT-1A: JP20.2, P3.1A (MOT-1A)
Z-MOT-1B: JP20.1, P3.1B (MOT-1B)
Z-MOT-2A: JP20.3, P3.2A (MOT-2A)
Z-MOT-2B: JP20.4, P3.2B (MOT-2B)
Z-MS1: P3.MS1, SJ14.1
Z-MS2: P3.MS2, SJ9.1
Z-MS3: P3.MS3, SJ4.1
Z-RESETSLEEP: P3.!RST (!RESET), P3.!SLP (!SLEEP)
Z-STEP: IC1.44 (PA7_AD7), P3.STEP
Z-STOP: IC1.9 (PE3_IUID), JP9.1
Z-STOP-SUPPLY: JP8.2, JP9.2

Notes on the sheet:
Motor Control X
Motor Control Y
Motor Control Z
Motor Control E
ISP
Thermistors
Endstops
Mosfets
Power Acc
Teensylu
Rev 0.9
Control for Reprap
Licensed under the Creative Commons Attributions ShareAlike 3.0 License
Extension Pin Headers
Power from ATX PS
5v Switching Regulator
SD and 3.3V Supply
*Note Stuff one connector or the other, not both.

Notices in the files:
Teensylu2-1.0.brd:
Licensed CC-BY-SA
